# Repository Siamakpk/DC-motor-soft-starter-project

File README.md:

# DC-motor-soft-starter-project

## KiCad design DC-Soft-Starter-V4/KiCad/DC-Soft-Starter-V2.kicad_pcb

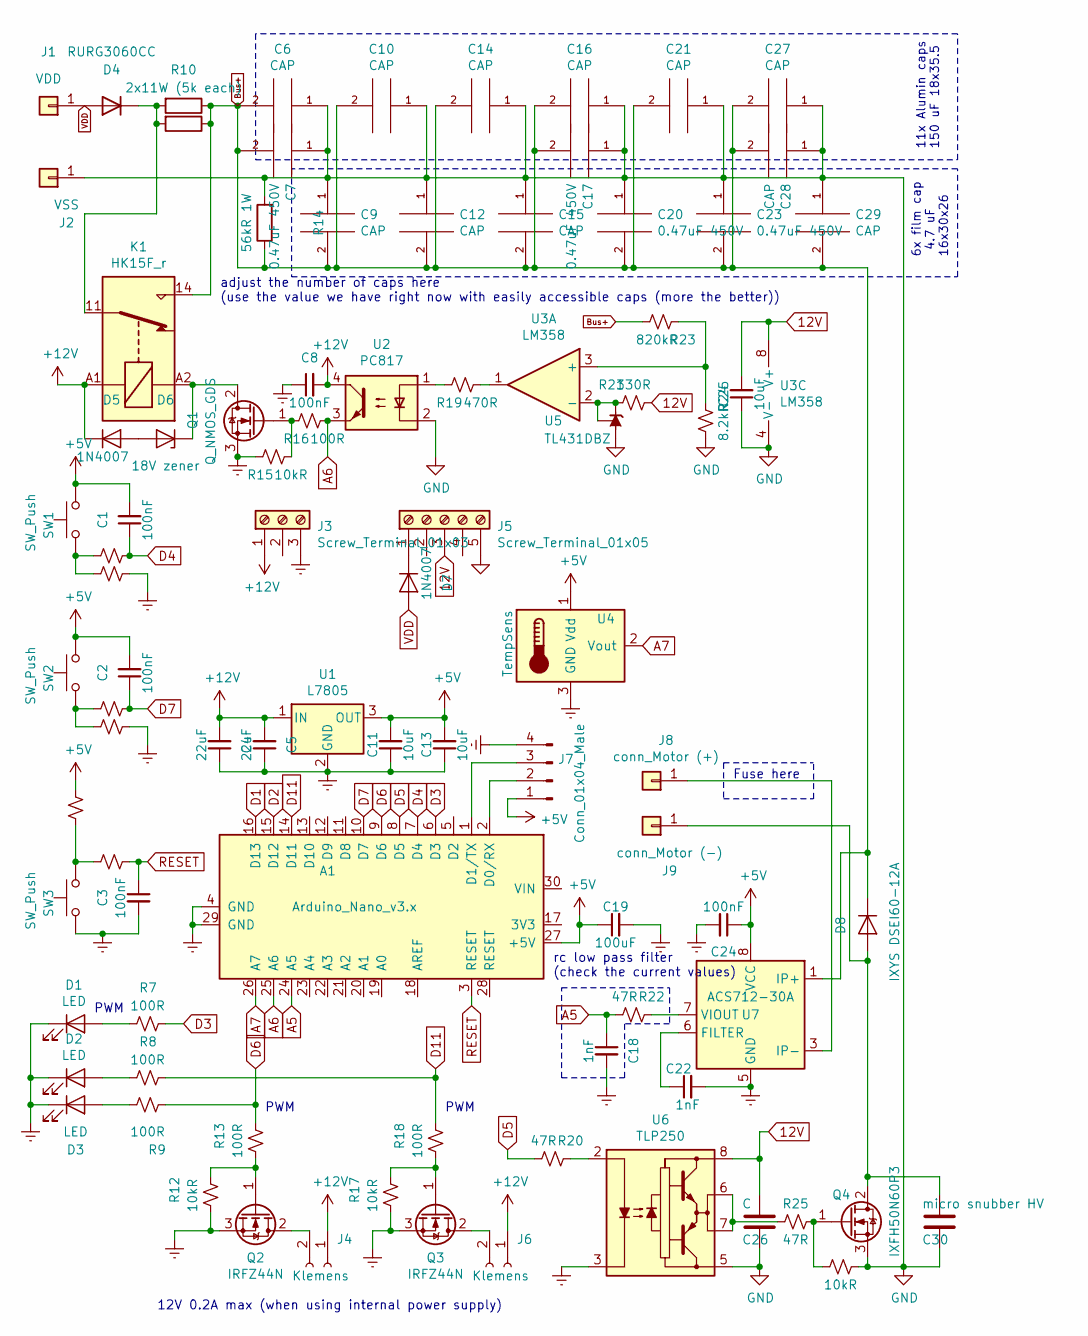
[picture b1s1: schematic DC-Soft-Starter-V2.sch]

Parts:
A1: Arduino_Nano_v3.x; Arduino_Nano
C1, C2, C3, C8, C24: 100nF; R_0805_2012Metric
C4, C5: 22uF; R_0805_2012Metric
C6: CAP; Cap_Parallel_2
C7, C17, C20, C23: 0.47uF 450V; C_1812_4532Metric
C9, C12, C15, C29: CAP; C_Rect_L29.0mm_W14.2mm_P27.50mm_MKT
C10, C14, C16, C27: CAP; Cap_Parallel
C11, C13, C25: 10uF; R_0805_2012Metric
C18, C22: 1nF; R_0805_2012Metric
C19: 100uF; CP_Radial_D6.3mm_P2.50mm
C21: CAP; Cap_Parallel_1
C26: C; R_0805_2012Metric
C28: CAP; Cap_12.8
C30: micro snubber HV; C_1812_4532Metric
D1, D2, D3: LED; LED_D3.0mm
D4: RURG3060CC; TO-247-3_Staggered_TabUp_1
D5, D7: 1N4007; D_SMA
D6: 18V zener; D_MELF
D8: IXYS DSEI60-12A; TO-247-2_Horizontal_TabDown
J1: VDD; M5
J2: VSS; M5
J3: Screw_Terminal_01x03; PinHeader_1x03_P2.54mm_Vertical
J4, J6: Klemens; PinHeader_1x02_P2.54mm_Vertical
J5: Screw_Terminal_01x05; PinHeader_1x05_P2.54mm_Vertical
J7: Conn_01x04_Male; PinHeader_1x04_P2.54mm_Vertical
J8: conn_Motor (+); M5
J9: conn_Motor (-); M5
K1: HK15F_r; Relay_SPDT_RAYEX-L90S
Q1: Q_NMOS_GDS; TO-252-3_cool
Q2, Q3: IRFZ44N; TO-252-3_cool
Q4: IXFH50N60P3; TO-247-3_Horizontal_TabDown
R1, R2, R3, R4, R5, R6, R7, R8, R9, R13, R16, R18: 100R; R_0805_2012Metric
R10, R11: 2x11W (5k each); R_Axial_Power_L48.0mm_W12.5mm_P55.88mm
R12, R15, R17, R26: 10kR; R_0805_2012Metric
R14: 56kR 1W; R_Axial_DIN0309_L9.0mm_D3.2mm_P15.24mm_Horizontal
R19: 470R; R_0805_2012Metric
R20, R22, R25: 47R; R_0805_2012Metric
R21: 330R; R_0805_2012Metric
R23: 820kR; R_Axial_DIN0309_L9.0mm_D3.2mm_P15.24mm_Horizontal
R24: 8.2kR; R_0805_2012Metric
SW1, SW2, SW3: SW_Push; PinHeader_1x02_P2.54mm_Vertical
U1: L7805; TO-252-3_cool
U2: PC817; DIP-4_W7.62mm
U3: LM358; SOIC-8_3.9x4.9mm_P1.27mm
U4: TempSens; TO-92
U5: TL431DBZ; SOT-23
U6: TLP250; DIP-8_W7.62mm
U7: ACS712-30A; SOIC-8_3.9x4.9mm_P1.27mm

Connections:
12V: C25.2, C26.1, J5.3, R21.1, U3.8 (V+), U6.8 (VCC)
+5V: A1.27 (+5V), C1.2, C2.2, C11.2, C13.2, C19.1, C24.1, J7.1, R1.2, SW1.2, SW2.2, U1.3 (OUT), U4.1 (Vdd), U7.8 (VCC)
+12V: C4.2, C5.2, C8.2, D5.1 (K), J3.1, J4.1, J6.1, K1.A1, U1.1 (IN), U2.4
A5: A1.24 (A5), C18.1, R22.2
A6: A1.25 (A6), R16.1, U2.3
A7: A1.26 (A7), U4.2 (Vout)
Bus+: C6.2, C7.2, C9.2, C10.2, C12.2, C14.2, C15.2, C16.2, C17.2, C20.2, C21.2, C23.2, C27.2, C28.2, C29.2, D8.1 (K), K1.14, R10.1, R11.1, R14.1, R23.1, U7.1 (IP+), U7.2 (IP+); also elsewhere on the board
D1: A1.16 (D13)
D2: A1.15 (D12)
D3: A1.6 (D3), R7.1
D4: A1.7 (D4), C1.1, R2.1
D5: A1.8 (D5), R20.2
D6: A1.9 (D6), R9.1, R13.1
D7: A1.10 (D7), C2.1, R4.1
D11: A1.14 (D11), R8.1, R18.1
GND: C6.1, C7.1, C9.1, C10.1, C12.1, C14.1, C15.1, C16.1, C17.1, C20.1, C21.1, C23.1, C25.1, C26.2, C27.1, C28.1, C29.1, C30.2, J2.1, J5.5, Q4.3 (S), R14.2, R24.1, R26.1, U2.2, U3.4 (V-), U5.3 (A), U6.5 (VEE); also elsewhere on the board
GNDREF: A1.4 (GND), A1.29 (GND), C3.2, C4.1, C5.1, C8.1, C11.1, C13.1, C18.2, C19.2, C22.2, C24.2, D1.1 (K), D2.1 (K), D3.1 (K), J3.3, J7.4, Q1.3 (S), Q2.3 (S), Q3.3 (S), R3.2, R5.2, R12.2, R15.2, R17.2, SW3.1, U1.2 (GND), U4.3 (GND), U6.3 (C), U7.5 (GND)
unnamed: A1.1 (D1/TX), J7.3
unnamed: A1.2 (D0/RX), J7.2
unnamed: C22.1, U7.6 (FILTER)
unnamed: C30.1, D8.2 (A), J9.1, Q4.2 (D)
unnamed: D1.2 (A), R7.2
unnamed: D2.2 (A), R8.2
unnamed: D3.2 (A), R9.2
unnamed: D4.2 (K), K1.11, R10.2, R11.2
unnamed: D5.2 (A), D6.2 (A)
unnamed: D6.1 (K), K1.A2, Q1.2 (D)
unnamed: D7.1 (K), J5.1
unnamed: J4.2, Q2.2 (D)
unnamed: J6.2, Q3.2 (D)
unnamed: J8.1, U7.3 (IP-), U7.4 (IP-)
unnamed: Q1.1 (G), R15.1, R16.2
unnamed: Q2.1 (G), R12.1, R13.2
unnamed: Q3.1 (G), R17.1, R18.2
unnamed: Q4.1 (G), R25.1, R26.2
unnamed: R1.1, R6.1, SW3.2
unnamed: R2.2, R3.1, SW1.1
unnamed: R4.2, R5.1, SW2.1
unnamed: R19.1, U3.1
unnamed: R19.2, U2.1
unnamed: R20.1, U6.2 (A)
unnamed: R21.2, U3.2 (-), U5.1 (K), U5.2 (REF)
unnamed: R22.1, U7.7 (VIOUT)
unnamed: R23.2, R24.2, U3.3 (+)
unnamed: R25.2, U6.6 (VO), U6.7 (VO)
RESET: A1.3 (RESET), C3.1, R6.2
VDD: D4.1 (A), D7.2 (A), J1.1

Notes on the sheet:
12V 0.2A max (when using internal power supply)
PWM
adjust the number of caps here (use the value we have right now with easily accessible caps (more the better))
Fuse here
rc low pass filter (check the current values)
6x film cap 4.7 uF 16x30x26
11x Alumin caps 150 uF 18x35.5

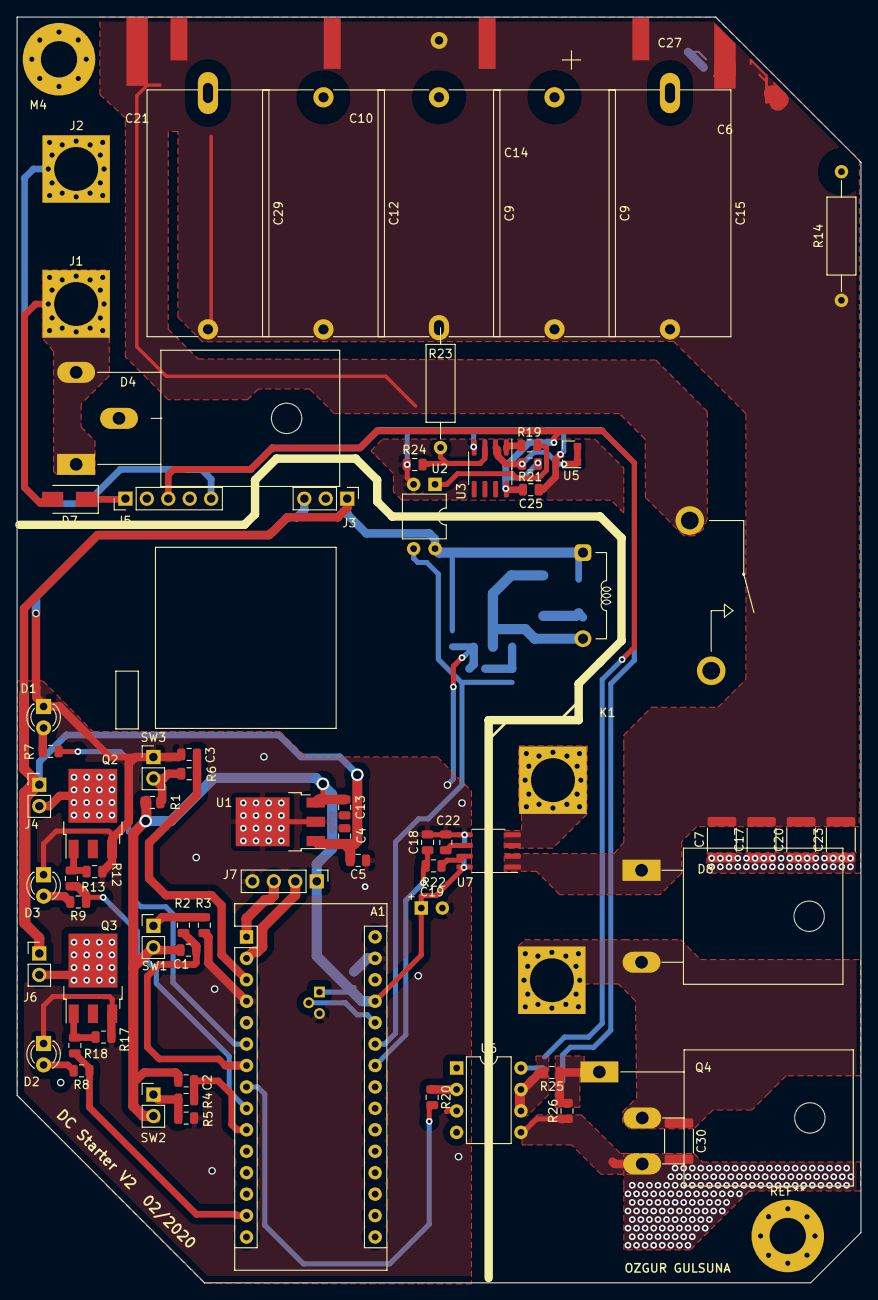
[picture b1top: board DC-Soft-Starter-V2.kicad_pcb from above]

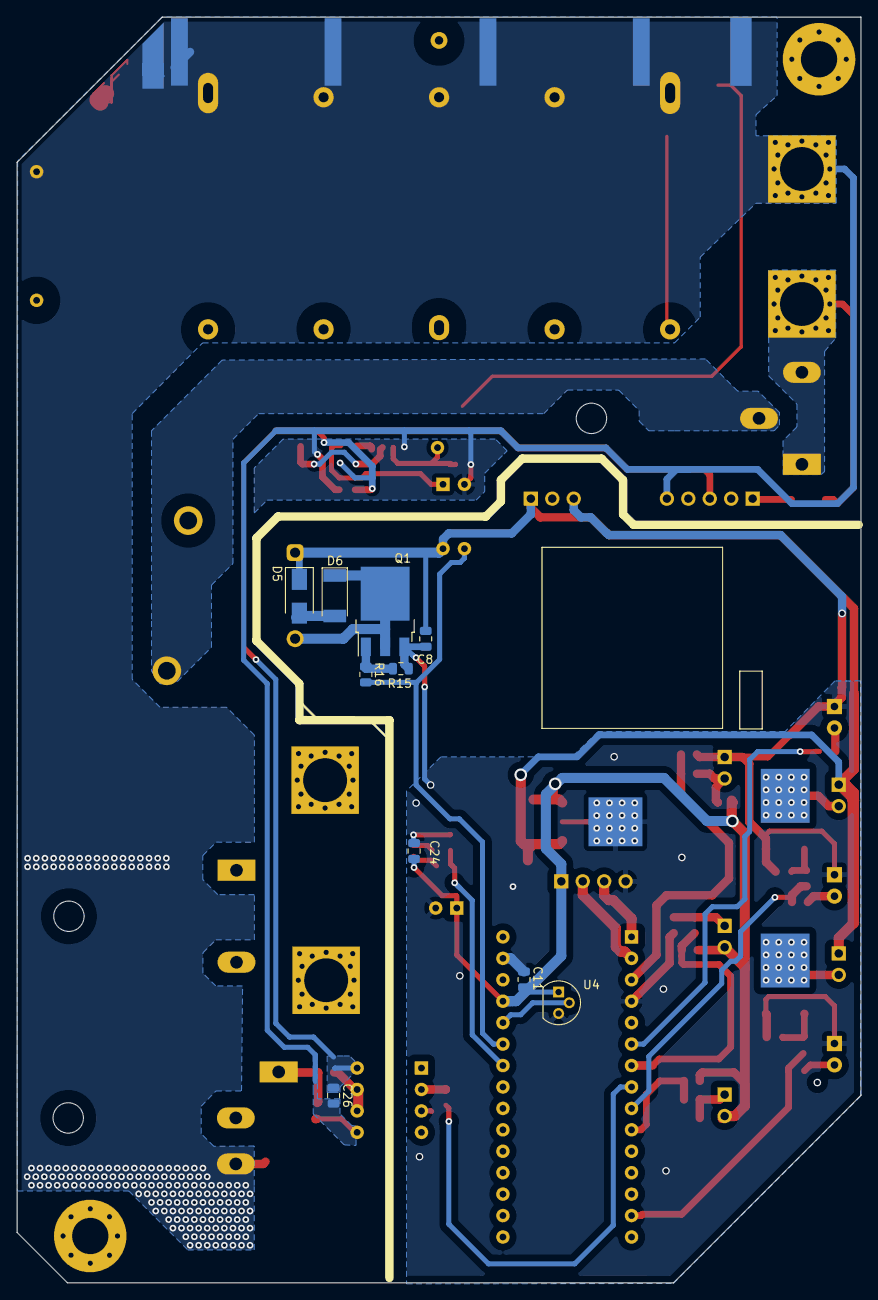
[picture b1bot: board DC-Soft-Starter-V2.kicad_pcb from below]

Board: 2 copper layers, 100.0 x 150.0 mm, 89 parts (10 on the bottom side), 45 nets.

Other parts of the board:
C9#2: CAP; C_Rect_L29.0mm_W14.2mm_P27.50mm_MKT
M4: MountingHole_4.3mm_M4_Pad_Via

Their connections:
Bus+: C9#2.2; also elsewhere on the board
GND: C9#2.1; also elsewhere on the board

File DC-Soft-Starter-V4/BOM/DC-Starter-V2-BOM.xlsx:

References | Item | Quantity | Part # | Value | Package | Digi-Key Part # | Digi-Key Link
A1 | Ard_Nano | 1 | - | - | THT | - | -
C18, C22 | Ceramic Cap | 2 | 50V | 1nF | SMD 0805 | 1276-1020-1-ND | https://www.digikey.com/product-detail/en/samsung-electro-me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
C1, C2, C3, C8, C24, | Ceramic Cap | 5 | 25V | 100nF | SMD 0805 | - | -
C7, C17, C20, C23 | Ceramic Cap | 4 | 450V | 0.47uF | SMD 1812 | 445-7927-1-ND | https://www.digikey.com/product-detail/en/tdk-corporation/CG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
C11, C13, C25, C26 | Ceramic Cap | 4 | 25V | 10uF | SMD 0805 | 1276-6454-1-ND | https://www.digikey.com/product-detail/en/samsung-electro-me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
C4, C5 | Ceramic Cap | 2 | 16V | 22uF | SMD 0805 | 1276-6780-1-ND | https://www.digikey.com/product-detail/en/samsung-electro-me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
C30 | Ceramic Cap | 1 | 1kV | 10nF | SMD 1812 | 399-16776-1-ND | https://www.digikey.com/product-detail/en/kemet/C1812C103KDR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
C30 | Ceramic Cap | 1 | 2kV | 1nF | SMD 1812 | 399-3447-1-ND | https://www.digikey.com/product-detail/en/kemet/C1812C102KGR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
C30 | Ceramic Cap | 1 | 2kV | 100pF | SMD 1812 | 478-12883-1-ND | https://www.digikey.com/product-detail/en/avx-corporation/18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
C9, C9, C12, C15, C29, | Film Cap | 5 | 450V | 2.2uF | THT | 1928-1596-ND | https://www.digikey.com/product-detail/en/wima/MKPF3Y42206B0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
C10, C14, C16, C27, C21, C6 | Elect. Cap | 11 | 450V | 150uF | THT | 1189-1353-ND | https://www.digikey.com/product-detail/en/450BXW150MEFC18X45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
C19 | Elect. Cap | 1 |  | 100uF/25V | THT | - | -
D1, D2, D3, | LED | 3 | - | - | THT | - | -
D4 | FastDiode | 1 | 650V | 150A | TO-247-3 | IDW75D65D1XKSA1-ND | https://www.digikey.com/product-detail/en/infineon-technolog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
D5, D7 | Diode | 2 | 1000V | 1A | SMD SMA | - | -
D6 | Zener Diode | 1 | 18V | 1W | SMD MELF | ZMY16-GS18GICT-ND | https://www.digikey.com/product-detail/en/vishay-semiconduct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
D8 | HyperFastDiode | 1 | 1200V | 52A | TO-247 | DSEI60-12A-ND | https://www.digikey.com/product-detail/en/ixys/DSEI60-12A/DS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
J1, J2, J8, J9 | Connector | 4 | - | - | M4
K1 | Relay | 1 | 12VDC | 30A | THT | 255-1719-ND | https://www.digikey.com/product-detail/en/panasonic-electric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
Q1, Q2, Q3 | Mosfet | 3 | NTD5865NL | 60V/40A | TO-252 | NTD5865NLT4GOSCT-ND | https://www.digikey.com/product-detail/en/on-semiconductor/N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
Q4 | PowerMosfet | 1 |  | 650V / 80A | TO-247-3 | IXFH80N65X2-ND | https://www.digikey.com/product-detail/en/ixys/IXFH80N65X2/I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
R1, R2, R3, R4, R5, R6, R7, R8, R9, R13, R16, R18, | Resistor | 12 |  | 100R | SMD 0805 | A130128CT-ND | https://www.digikey.com/product-detail/en/yageo/RC0805JR-071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
R12, R15, R17, R26, | Resistor | 4 |  | 10kR | SMD 0805 | - | -
R14, | Resistor | 1 |  | 56kR | THT | - | -
R19, | Resistor | 1 |  | 470R | SMD 0805 | - | -
R20, R22, R25, | Resistor | 3 |  | 47R | SMD 0805 | - | -
R21, | Resistor | 1 |  | 330R | SMD 0805 | - | -
R23, | Resistor | 1 |  | 820kR | THT | - | -
R24, | Resistor | 1 |  | 8.2kR | SMD 0805 | - | -
R10, | PowerResistor | 1 |  | 1kR | TO-220 | 696-1336-ND | https://www.digikey.com/product-detail/en/riedon/PF2205-1KF1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
SW1, SW2, SW3, | Button | 3 |  | SW_Push | - | - | -
U1, | Voltage Regulator | 1 |  | 78M05 | TO-252 | - | -
U2, | Opto-Coupler | 1 |  | PC817 | DIP | - | -
U3, | Op-Amp | 1 |  | LM358 | SOIC8 | 497-1591-1-ND | https://www.digikey.com/product-detail/en/stmicroelectronics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
U4, | Temp Sensor | 1 |  | MCP9701 | TO-92 | MCP9701-E/TO-ND | https://www.digikey.com/product-detail/en/microchip-technolo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
U5, | Voltage Reference | 1 |  | TL431A | SOT-23-3 | 296-18864-1-ND | https://www.digikey.com/product-detail/en/texas-instruments/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
U6, | Gate Driver | 1 |  | TLP350 | DIP | - | -
U7, | Current Sensor | 1 |  | ACS712-30A | SOIC8 | 620-1191-1-ND | https://www.digikey.com/product-detail/en/allegro-microsyste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
Component Count : |  | 90
Date: |  | 43874
Avaliable | Unavaliable

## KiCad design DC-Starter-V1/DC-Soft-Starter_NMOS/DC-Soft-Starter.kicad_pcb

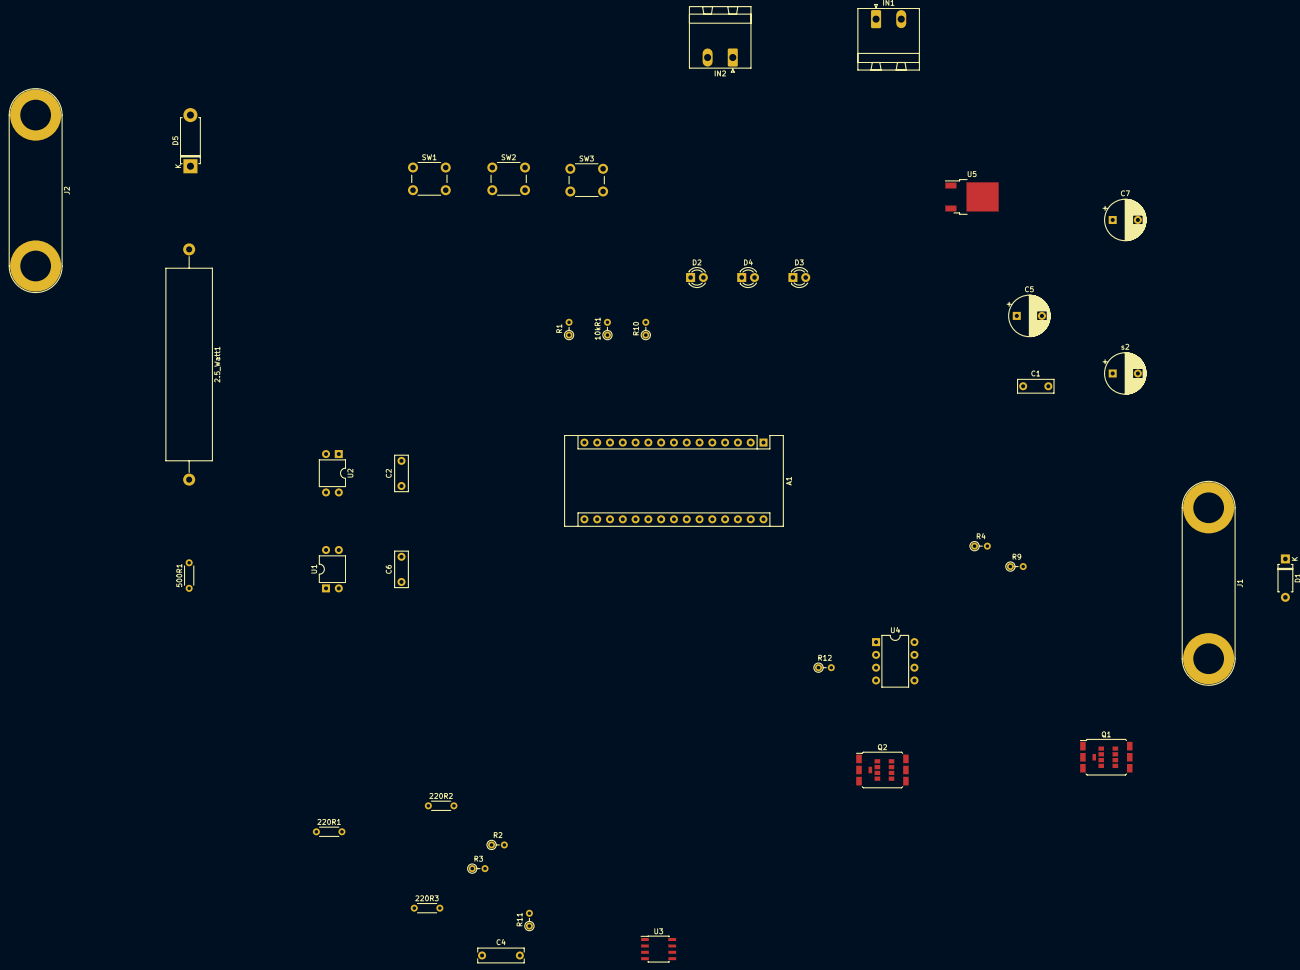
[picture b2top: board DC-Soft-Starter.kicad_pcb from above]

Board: 2 copper layers, 41 parts (0 on the bottom side), 30 nets, no tracks yet.

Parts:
2.5_Watt1: 22kR; R_Axial_Power_L38.0mm_W9.0mm_P45.72mm
10kR1: R_US; R_Axial_DIN0204_L3.6mm_D1.6mm_P2.54mm_Vertical
220R1, 220R2, 220R3: R_US; R_Axial_DIN0204_L3.6mm_D1.6mm_P5.08mm_Horizontal
500R1: fine adj res; R_Axial_DIN0204_L3.6mm_D1.6mm_P5.08mm_Horizontal
A1: Arduino_Nano
C1, C2, C6: 100nF; C_Rect_L7.0mm_W2.5mm_P5.00mm
C4: 100uf; C_Rect_L9.0mm_W2.7mm_P7.50mm_MKT
C5: 220uF; CP_Radial_D8.0mm_P5.00mm
C7: 100uF; CP_Radial_D8.0mm_P5.00mm
D1: 1N4007; D_A-405_P7.62mm_Horizontal
D2, D3, D4: LED; LED_D3.0mm_Clear
D5: DIODE; D_5W_P10.16mm_Horizontal
IN1, IN2: 15 VDC; PhoenixContact_MSTBA_2,5_2-G_1x02_P5.00mm_Horizontal
J1, J2: Screw_Terminal_01x02; Banana_Jack_2Pin
Q1, Q2: IXFH40N30; DirectFET_L8
R1, R10: 10kR; R_Axial_DIN0204_L3.6mm_D1.6mm_P2.54mm_Vertical
R2, R3, R4: R_US; R_Axial_DIN0204_L3.6mm_D1.6mm_P2.54mm_Vertical
R9, R12: 4.7R; R_Axial_DIN0204_L3.6mm_D1.6mm_P2.54mm_Vertical
R11: 220R; R_Axial_DIN0204_L3.6mm_D1.6mm_P2.54mm_Vertical
SW1, SW2, SW3: SW_DPST_x2; SW_PUSH_6mm_H9.5mm
U1, U2: PC817; DIP-4_W7.62mm
U3: ACS712 30A; SOIC-8_3.9x4.9mm_P1.27mm
U4: TLP350; DIP-8_W7.62mm
U5: LM2575T; TO-252-2
s2: 1nF; CP_Radial_D8.0mm_P5.00mm

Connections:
15V: C2.1, C6.1, U2.4, U4.8
+5V: A1.27, C1.1, C4.1, C7.1, R2.1, R3.1, R4.1, U1.4, U3.8, U5.3
+15V: C5.1, IN1.2, IN2.2, U5.1
GNDREF: A1.4, A1.29, C4.2, C5.2, C7.2, D2.1, D3.1, D4.1, IN1.1, IN2.1, R1.2, SW1.2, SW2.2, U3.5, U4.3, U5.2, s2.1
unnamed: 2.5_Watt1.1, D1.2
unnamed: 2.5_Watt1.2, 500R1.1, U1.1
unnamed: 10kR1.1, C6.2, Q1.3, Q2.3, R10.2, U4.5
unnamed: 10kR1.2, Q2.2, R12.1
unnamed: 220R1.1, D2.2
unnamed: 220R1.2, A1.12
unnamed: 220R2.1, D3.2
unnamed: 220R2.2, A1.11
unnamed: 220R3.1, D4.2
unnamed: 220R3.2, A1.10
unnamed: 500R1.2, J1.1, U2.2, U3.3, U3.4
unnamed: A1.8, R11.1
unnamed: A1.13, R4.2, SW1.1
unnamed: A1.14, R3.2
unnamed: A1.15, R2.2, SW2.1
unnamed: A1.16, C1.2, R1.1, U1.3
unnamed: A1.23, U3.7
unnamed: C2.2, R9.1, U2.3
unnamed: D1.1, D5.2, J1.2, J2.1
unnamed: D5.1, J2.2, Q2.1
unnamed: Q1.1, U3.1, U3.2
unnamed: Q1.2, R9.2, R10.1
unnamed: R11.2, U4.2
unnamed: R12.2, U4.6, U4.7
unnamed: U1.2, U2.1
unnamed: U3.6, s2.2

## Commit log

2019-03-22 Codes before PCB design
2019-03-22 no message
2020-09-02 haftalık rapor - deneme
2020-09-02 deneme
2020-09-02 pic size adj
2020-09-02 pic update
2020-09-02 Haftalık rapor [1-7 eylü]
2020-09-08 Firmware Update
2021-04-05 Firmware update after short circuit protection
